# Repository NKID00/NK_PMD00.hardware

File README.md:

## NK_PortableMultifunctionalDevice00

`便携多功能设备 00` 其实就是电子辞典。

市面上的电子辞典太贵还有平时用不到的多余功能，于是打算自己做一个。

这个项目大约从 2020 年 5 月就开始了，目前硬件部分已经完成了约 10%。

此仓库为硬件部分，软件部分请前往 [NK_PMD00.software](https://github.com/NKID00/NK_PMD00.software)。

`pmd00/` 是电路部分，使用 KiCAD 设计，采用了树莓派 zero 和 128x64 液晶屏。

` ` 是外壳部分。

## 版权

版权所有 © 2020-2021 NKID00

使用 CC-BY-SA 4.0 进行许可。

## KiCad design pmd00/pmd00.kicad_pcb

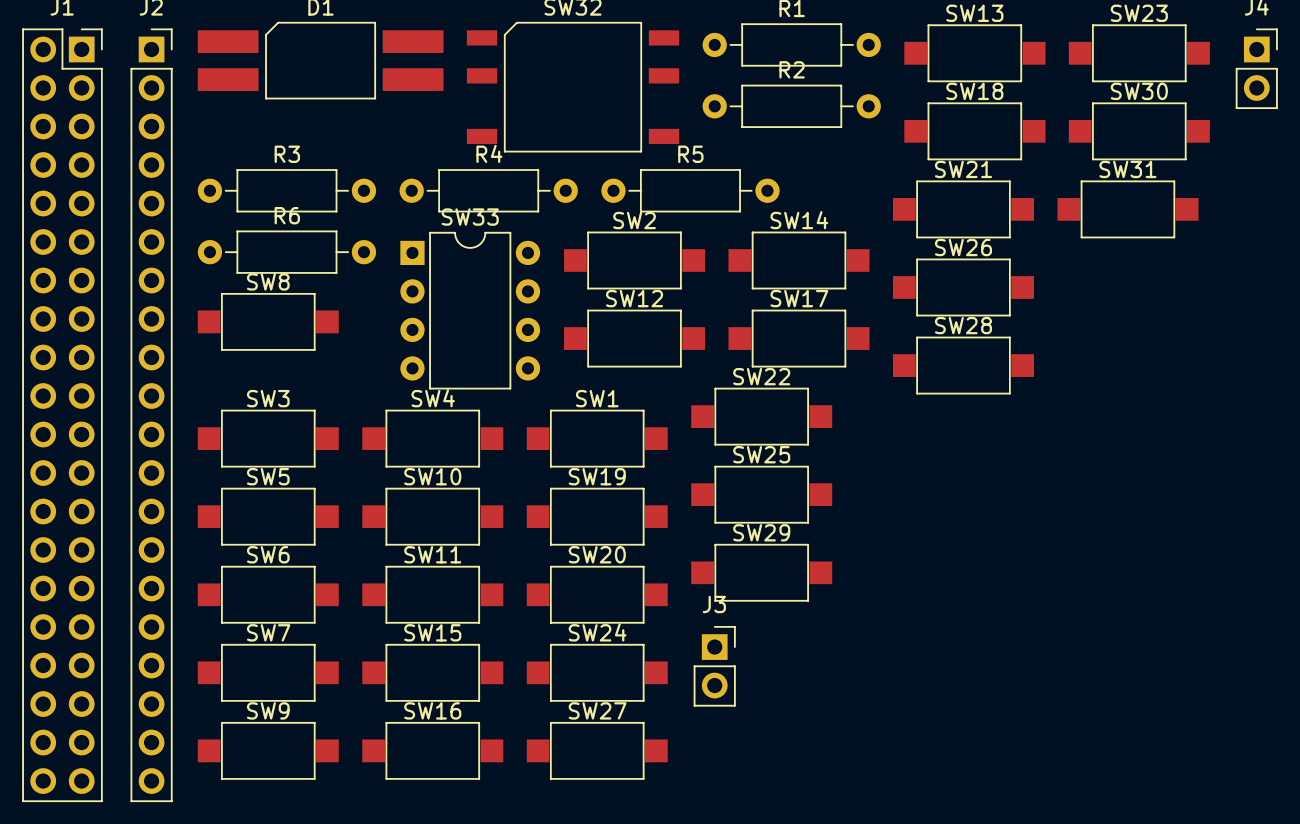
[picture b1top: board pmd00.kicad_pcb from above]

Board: 2 copper layers, 44 parts (0 on the bottom side), 30 nets, no tracks yet.

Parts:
D1: LED_RGBA; LED_RGB_P4mm
J1: Raspberry_Pi_Zero; PinSocket_2x20_P2.54mm_Vertical
J2: LCD12864; PinSocket_1x20_P2.54mm_Vertical
J3: Conn_Battery_In; PinSocket_1x02_P2.54mm_Vertical
J4: Conn_Battery_Out; PinSocket_1x02_P2.54mm_Vertical
R1, R2, R3, R4: 220R; R_Axial_DIN0207_L6.3mm_D2.5mm_P10.16mm_Horizontal
R5: 470R; R_Axial_DIN0207_L6.3mm_D2.5mm_P10.16mm_Horizontal
R6: 1K; R_Axial_DIN0207_L6.3mm_D2.5mm_P10.16mm_Horizontal
SW1: SW_Key_1; SW_SPST_CK_RS282G05A3
SW2: SW_Key_2; SW_SPST_CK_RS282G05A3
SW3: SW_Key_3; SW_SPST_CK_RS282G05A3
SW4: SW_Key_4; SW_SPST_CK_RS282G05A3
SW5: SW_Key_0; SW_SPST_CK_RS282G05A3
SW6: SW_Key_Q; SW_SPST_CK_RS282G05A3
SW7: SW_Key_W; SW_SPST_CK_RS282G05A3
SW8: SW_Key_E; SW_SPST_CK_RS282G05A3
SW9: SW_Key_R; SW_SPST_CK_RS282G05A3
SW10: SW_Key_T; SW_SPST_CK_RS282G05A3
SW11: SW_Key_Y; SW_SPST_CK_RS282G05A3
SW12: SW_Key_U; SW_SPST_CK_RS282G05A3
SW13: SW_Key_I; SW_SPST_CK_RS282G05A3
SW14: SW_Key_O; SW_SPST_CK_RS282G05A3
SW15: SW_Key_P; SW_SPST_CK_RS282G05A3
SW16: SW_Key_A; SW_SPST_CK_RS282G05A3
SW17: SW_Key_S; SW_SPST_CK_RS282G05A3
SW18: SW_Key_D; SW_SPST_CK_RS282G05A3
SW19: SW_Key_F; SW_SPST_CK_RS282G05A3
SW20: SW_Key_G; SW_SPST_CK_RS282G05A3
SW21: SW_Key_H; SW_SPST_CK_RS282G05A3
SW22: SW_Key_J; SW_SPST_CK_RS282G05A3
SW23: SW_Key_K; SW_SPST_CK_RS282G05A3
SW24: SW_Key_L; SW_SPST_CK_RS282G05A3
SW25: SW_Key_Z; SW_SPST_CK_RS282G05A3
SW26: SW_Key_X; SW_SPST_CK_RS282G05A3
SW27: SW_Key_C; SW_SPST_CK_RS282G05A3
SW28: SW_Key_V; SW_SPST_CK_RS282G05A3
SW29: SW_Key_B; SW_SPST_CK_RS282G05A3
SW30: SW_Key_N; SW_SPST_CK_RS282G05A3
SW31: SW_Key_M; SW_SPST_CK_RS282G05A3
SW32: SW_5D
SW33: SW_DIP_x04; DIP-8_W7.62mm

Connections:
+5V: D1.4, J1.2, J2.2, J2.4, SW33.2
GND: J1.6, J2.1, J2.20
Key_Column_1: J1.3, SW1.1, SW6.1, SW15.1, SW16.1, SW25.1, SW32.5
Key_Column_2: J1.5, SW2.1, SW7.1, SW14.1, SW17.1, SW24.1, SW26.1, SW32.4
Key_Column_3: J1.7, SW3.1, SW8.1, SW13.1, SW18.1, SW23.1, SW27.1, SW32.6
Key_Column_4: J1.11, SW4.1, SW9.1, SW12.1, SW19.1, SW22.1, SW28.1, SW31.1, SW32.2
Key_Column_5: J1.13, SW5.1, SW10.1, SW11.1, SW20.1, SW21.1, SW29.1, SW30.1, SW32.3
Key_Row_5D: J1.35, SW32.1
Key_Row_Left_1: J1.15, SW1.2, SW2.2, SW3.2, SW4.2, SW5.2
Key_Row_Left_2: J1.19, SW6.2, SW7.2, SW8.2, SW9.2, SW10.2
Key_Row_Left_3: J1.21, SW16.2, SW17.2, SW18.2, SW19.2, SW20.2
Key_Row_Left_4: J1.23, SW25.2, SW26.2, SW27.2, SW28.2, SW29.2
Key_Row_Right_1: J1.29, SW11.2, SW12.2, SW13.2, SW14.2, SW15.2
Key_Row_Right_2: J1.31, SW21.2, SW22.2, SW23.2, SW24.2
Key_Row_Right_3: J1.33, SW30.2, SW31.2
LCD_BL: R4.1, R6.1, SW33.5
LCD_SCLK: J1.18, J2.6
LCD_SID: J1.16, J2.5
unnamed: D1.1, R1.1
unnamed: D1.2, R2.1
unnamed: D1.3, R3.1
unnamed: J2.19, R4.2
unnamed: J3.1, SW33.1
unnamed: J3.2, J4.2
unnamed: J4.1, SW33.8
unnamed: R5.1, SW33.6, SW33.7
unnamed: R5.2, R6.2, SW33.3, SW33.4
~LED_B~: J1.40, R3.2
~LED_G~: J1.38, R2.2
~LED_R~: J1.37, R1.2

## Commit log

2021-02-20 ✨Initial commit
2021-02-23 🔧修改措辞
2021-02-24 🔧明确进度
